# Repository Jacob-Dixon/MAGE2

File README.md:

# MAGE2 Project Documentation
This repository contains all documentation files for the MAGE 2 system. [Please visit our wiki page](https://github.com/Jacob-Dixon/MAGE2/wiki) to learn more about the MAGE 2 system.

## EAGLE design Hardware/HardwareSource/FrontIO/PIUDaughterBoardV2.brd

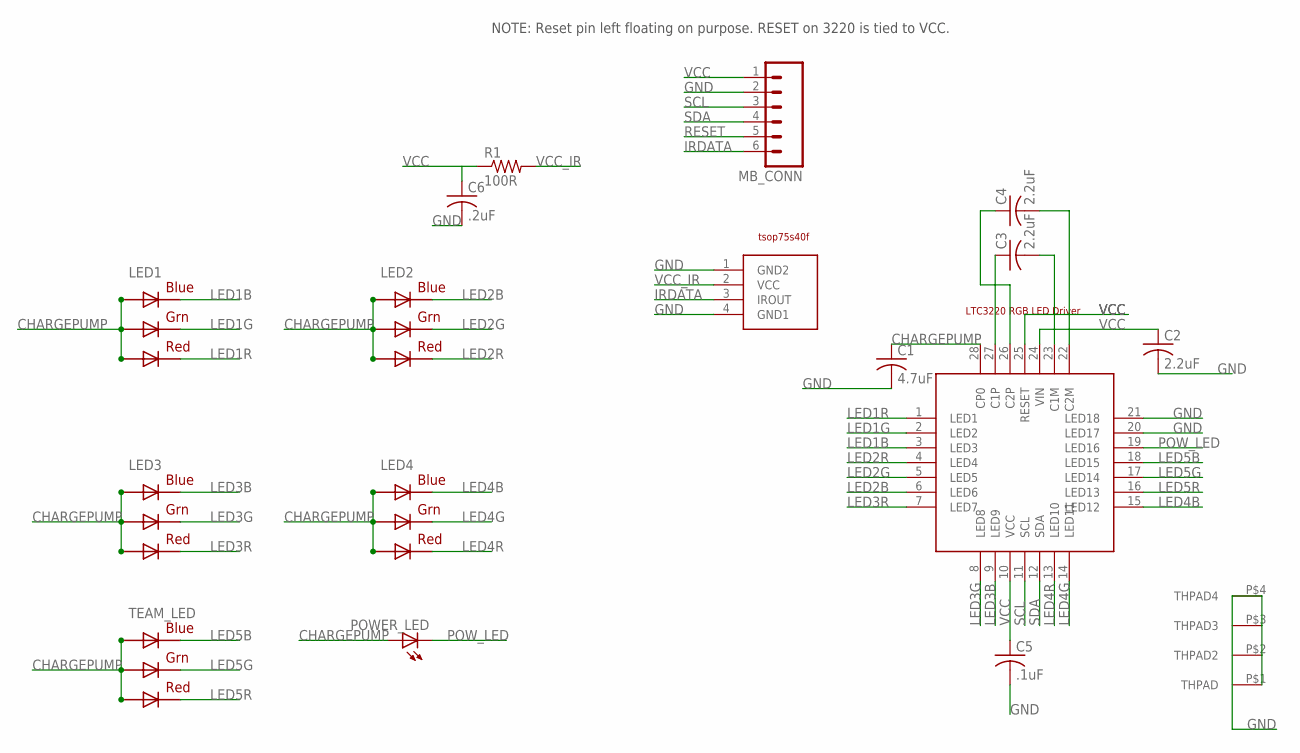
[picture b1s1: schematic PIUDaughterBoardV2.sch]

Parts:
C1: 4.7uF; C0603
C2, C3, C4: 2.2uF; C0603
C5: .1uF; C0603
C6: .2uF; C0603
LED1, LED2, LED3, LED4: RGBLED5050
MB_CONN: M06SMD_MALE; 1X06_SMD_MALE
POWER_LED: LEDCHIPLED_0805; CHIPLED_0805
R1: 100R; R0603
TEAM_LED: RGBLED5050
U$1: TSOP75S40F
U$3: LTC3220

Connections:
CHARGEPUMP: C1.1, LED1.1 (GREEN_A), LED1.2 (RED_A), LED1.3 (BLUE_A), LED2.1 (GREEN_A), LED2.2 (RED_A), LED2.3 (BLUE_A), LED3.1 (GREEN_A), LED3.2 (RED_A), LED3.3 (BLUE_A), LED4.1 (GREEN_A), LED4.2 (RED_A), LED4.3 (BLUE_A), POWER_LED.A, TEAM_LED.1 (GREEN_A), TEAM_LED.2 (RED_A), TEAM_LED.3 (BLUE_A), U$3.28 (CP0)
GND: C1.2, C2.2, C5.2, C6.2, MB_CONN.2, U$1.1 (GND2), U$1.4 (GND1), U$3.20 (LED17), U$3.21 (LED18), U$3.P$1 (THPAD), U$3.P$2 (THPAD2), U$3.P$3 (THPAD3), U$3.P$4 (THPAD4)
IRDATA: MB_CONN.6, U$1.3 (IROUT)
LED1B: LED1.4 (BLUE_C), U$3.3 (LED3)
LED1G: LED1.6 (GREEN_C), U$3.2 (LED2)
LED1R: LED1.5 (RED_C), U$3.1 (LED1)
LED2B: LED2.4 (BLUE_C), U$3.6 (LED6)
LED2G: LED2.6 (GREEN_C), U$3.5 (LED5)
LED2R: LED2.5 (RED_C), U$3.4 (LED4)
LED3B: LED3.4 (BLUE_C), U$3.9 (LED9)
LED3G: LED3.6 (GREEN_C), U$3.8 (LED8)
LED3R: LED3.5 (RED_C), U$3.7 (LED7)
LED4B: LED4.4 (BLUE_C), U$3.15 (LED12)
LED4G: LED4.6 (GREEN_C), U$3.14 (LED11)
LED4R: LED4.5 (RED_C), U$3.13 (LED10)
LED5B: TEAM_LED.4 (BLUE_C), U$3.18 (LED15)
LED5G: TEAM_LED.6 (GREEN_C), U$3.17 (LED14)
LED5R: TEAM_LED.5 (RED_C), U$3.16 (LED13)
unnamed: C4.2, U$3.22 (C2M)
unnamed: C3.2, U$3.23 (C1M)
unnamed: C3.1, U$3.27 (C1P)
unnamed: C4.1, U$3.26 (C2P)
POW_LED: POWER_LED.C, U$3.19 (LED16)
RESET: MB_CONN.5
SCL: MB_CONN.3, U$3.11 (SCL)
SDA: MB_CONN.4, U$3.12 (SDA)
VCC: C2.1, C5.1, C6.1, MB_CONN.1, R1.1, U$3.10 (VCC), U$3.24 (VIN), U$3.25 (RESET)
VCC_IR: R1.2, U$1.2 (VCC)

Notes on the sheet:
NOTE: Reset pin left floating on purpose. RESET on 3220 is tied to VCC.

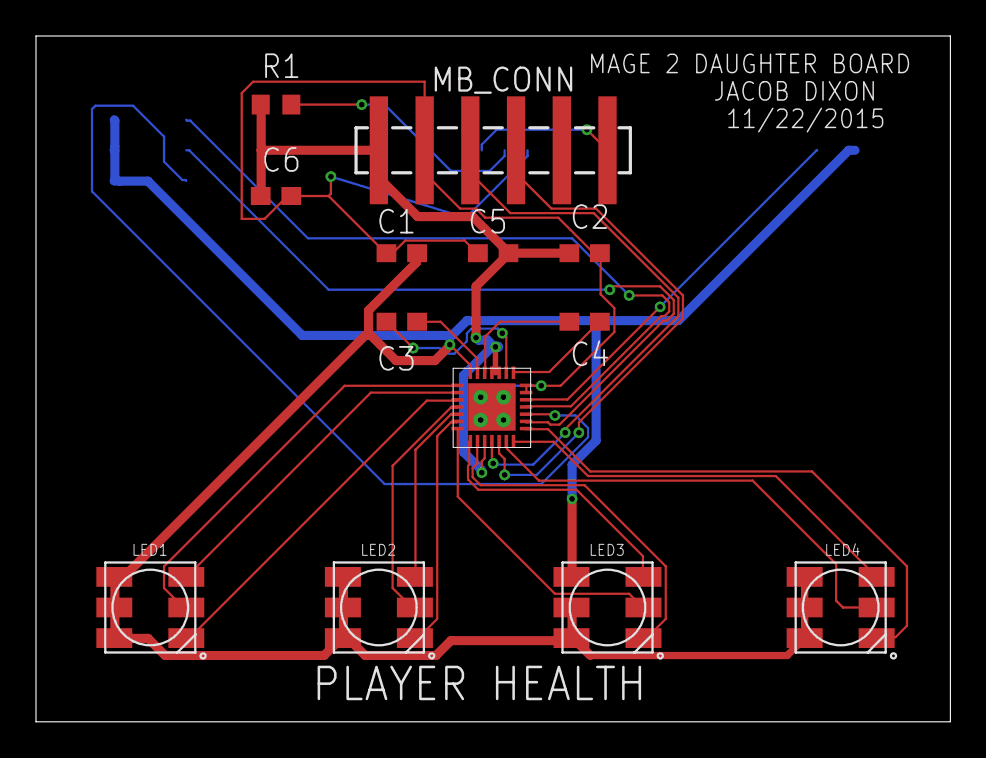
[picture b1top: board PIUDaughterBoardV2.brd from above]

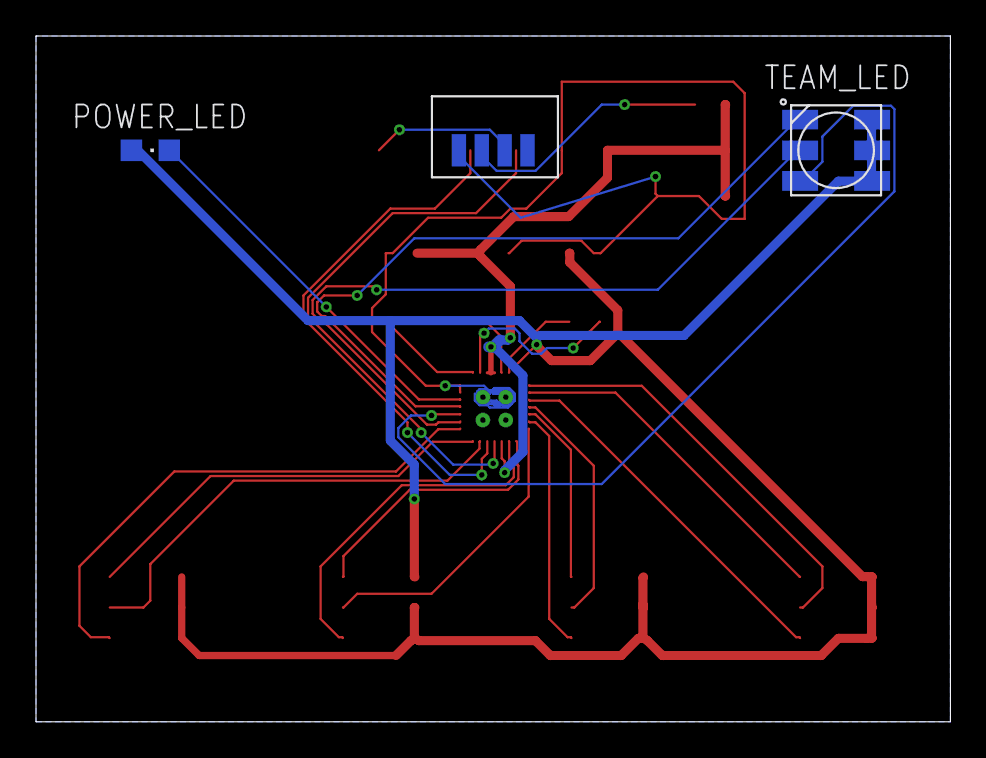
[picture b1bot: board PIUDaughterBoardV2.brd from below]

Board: 2 copper layers, 50.8 x 38.1 mm, 16 parts (3 on the bottom side), 27 nets.

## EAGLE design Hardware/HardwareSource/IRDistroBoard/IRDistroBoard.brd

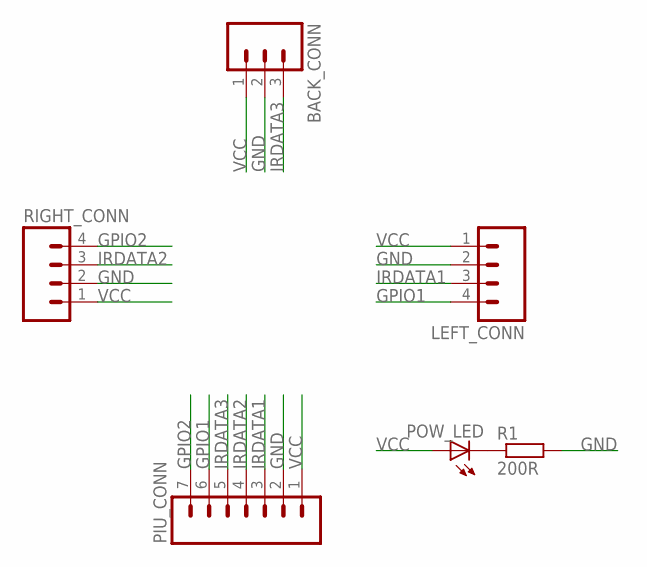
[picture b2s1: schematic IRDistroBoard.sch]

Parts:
BACK_CONN: M03PTH; 1X03
LEFT_CONN: M04PTH; 1X04
PIU_CONN: M07; 1X07
POW_LED: LEDCHIPLED_0805; CHIPLED_0805
R1: 200R; R805
RIGHT_CONN: M04PTH; 1X04

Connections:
GND: BACK_CONN.2, LEFT_CONN.2, PIU_CONN.2, R1.2, RIGHT_CONN.2
GPIO1: LEFT_CONN.4, PIU_CONN.6
GPIO2: PIU_CONN.7, RIGHT_CONN.4
IRDATA1: LEFT_CONN.3, PIU_CONN.3
IRDATA2: PIU_CONN.4, RIGHT_CONN.3
IRDATA3: BACK_CONN.3, PIU_CONN.5
unnamed: POW_LED.C, R1.1
VCC: BACK_CONN.1, LEFT_CONN.1, PIU_CONN.1, POW_LED.A, RIGHT_CONN.1

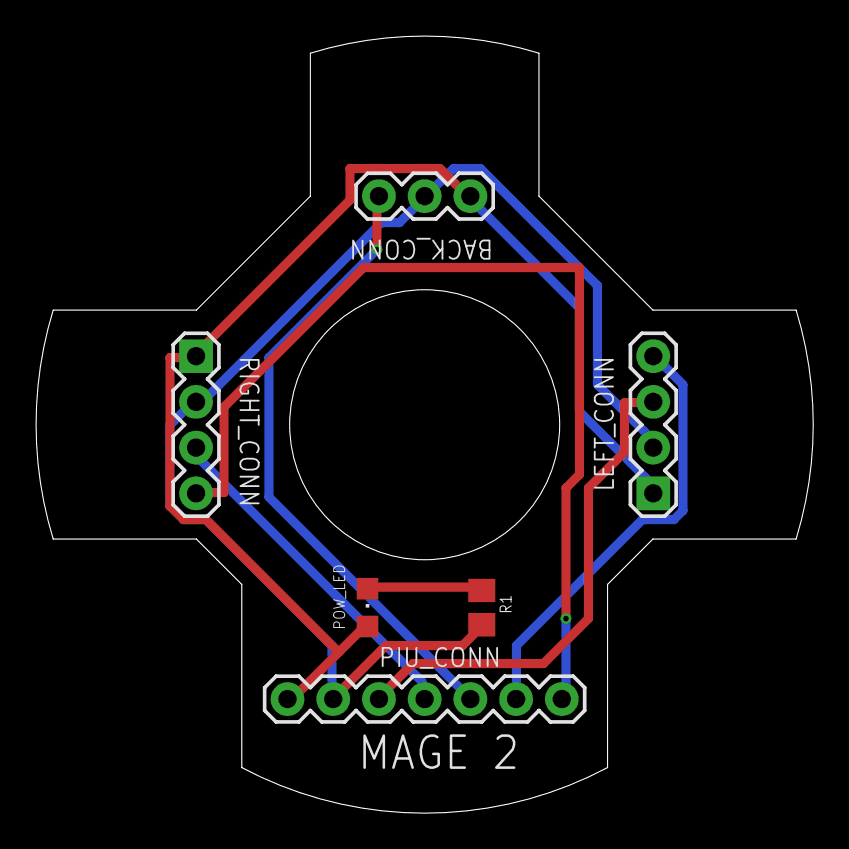
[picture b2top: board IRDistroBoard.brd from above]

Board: 2 copper layers, 43.2 x 43.2 mm, 6 parts (0 on the bottom side), 8 nets.

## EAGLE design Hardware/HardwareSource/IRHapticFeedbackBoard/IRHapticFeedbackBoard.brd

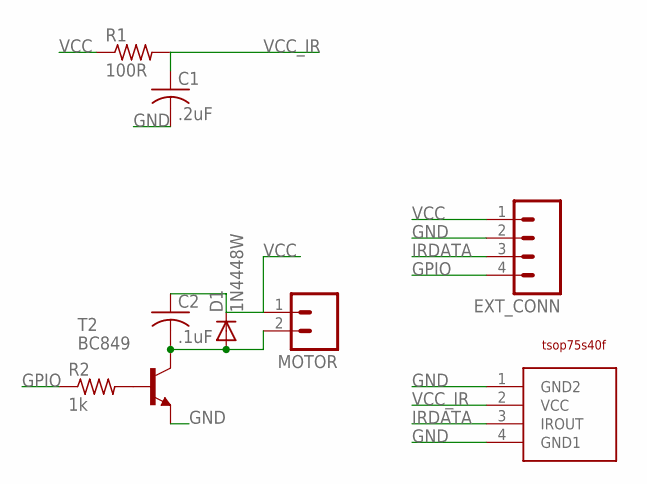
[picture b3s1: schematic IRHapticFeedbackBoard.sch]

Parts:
C1: .2uF; C0603
C2: .1uF; C0603
D1: 1N4448W; SOD-123
EXT_CONN: M04PTH; 1X04
MOTOR: M02PTH; 1X02
R1: 100R; R0603
R2: 1k; R0603
T2: BC849; SOT23
U$1: TSOP75S40F

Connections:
GND: C1.2, EXT_CONN.2, T2.2 (E), U$1.1 (GND2), U$1.4 (GND1)
GPIO: EXT_CONN.4, R2.1
IRDATA: EXT_CONN.3, U$1.3 (IROUT)
unnamed: R2.2, T2.1 (B)
unnamed: C2.2, D1.A, MOTOR.2, T2.3 (C)
VCC: C2.1, D1.C, EXT_CONN.1, MOTOR.1, R1.1
VCC_IR: C1.1, R1.2, U$1.2 (VCC)

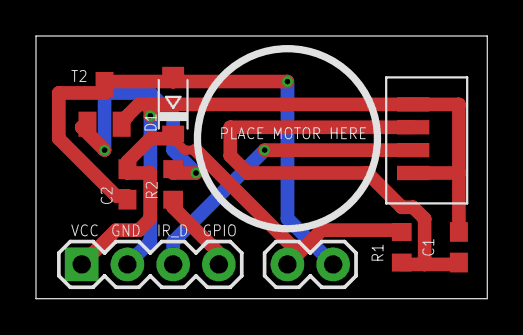
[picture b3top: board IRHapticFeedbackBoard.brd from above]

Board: 2 copper layers, 25.1 x 14.6 mm, 9 parts (0 on the bottom side), 7 nets.

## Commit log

2015-09-27 :circus_tent: Added .gitattributes
2015-09-27 Init README
    Added Readme page for the documentation drop.
2015-09-27 changed style
    changed wording
2015-09-27 updated
    forgot some wording.
2015-09-27 Added Team Logo in WikiResources
2015-09-27 Fixed formatting in readme
2015-10-06 fixed typo in readme
2015-10-06 Added Protocols
    Added MAGE Bluetooth and IR protocol documentation
2015-10-13 Added MAGE2 Block Diagram photo
    Photo for block diagram added
2015-10-13 Updated IR protocol
2015-11-11 Added Peripheral PCB Photos
2015-11-11 Added PIU PCB Family photo (V1)
2015-11-11 Added Enclosure Photos
2015-11-11 Added photos of enclosure
2015-11-15 updated with most recent PIU enclosure source files
2015-11-15 Created hardware root folder. Added PIU V2 BOM
2015-11-16 updated Haptic Feedback Case
2015-11-22 Added Bill of materials for PIU
2015-11-22 Added hardware sources for PIU, IRHapticFeedback,IRDistroboard, FrontIO
2015-11-22 Added reference weapon hardware source files
2015-11-22 Added BOM for peripheral PCB's
2015-11-22 Added PCB Errata document
2015-12-09 Added Product Photos
2016-02-08 added spells
2016-03-21 Fixed Protocols
    Removed outdated BT spreadsheet
    Fixed bit encoding
    Fixed protocols

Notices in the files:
parts and their libraries:
BryanConnectors: Licensing: Creative Commons ShareAlike 4.0 International - https://creativecommons.org/licenses/by-sa/4.0
